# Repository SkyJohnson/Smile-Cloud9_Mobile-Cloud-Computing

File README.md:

# Smile-Cloud9_Mobile-Cloud-Computing
Design for cloud-based rovers to perform image processing over a wireless distributed-computing framework using Jetson Nano and Arduino

This branch contains pictures and screenshots for verification and presentation purposes.

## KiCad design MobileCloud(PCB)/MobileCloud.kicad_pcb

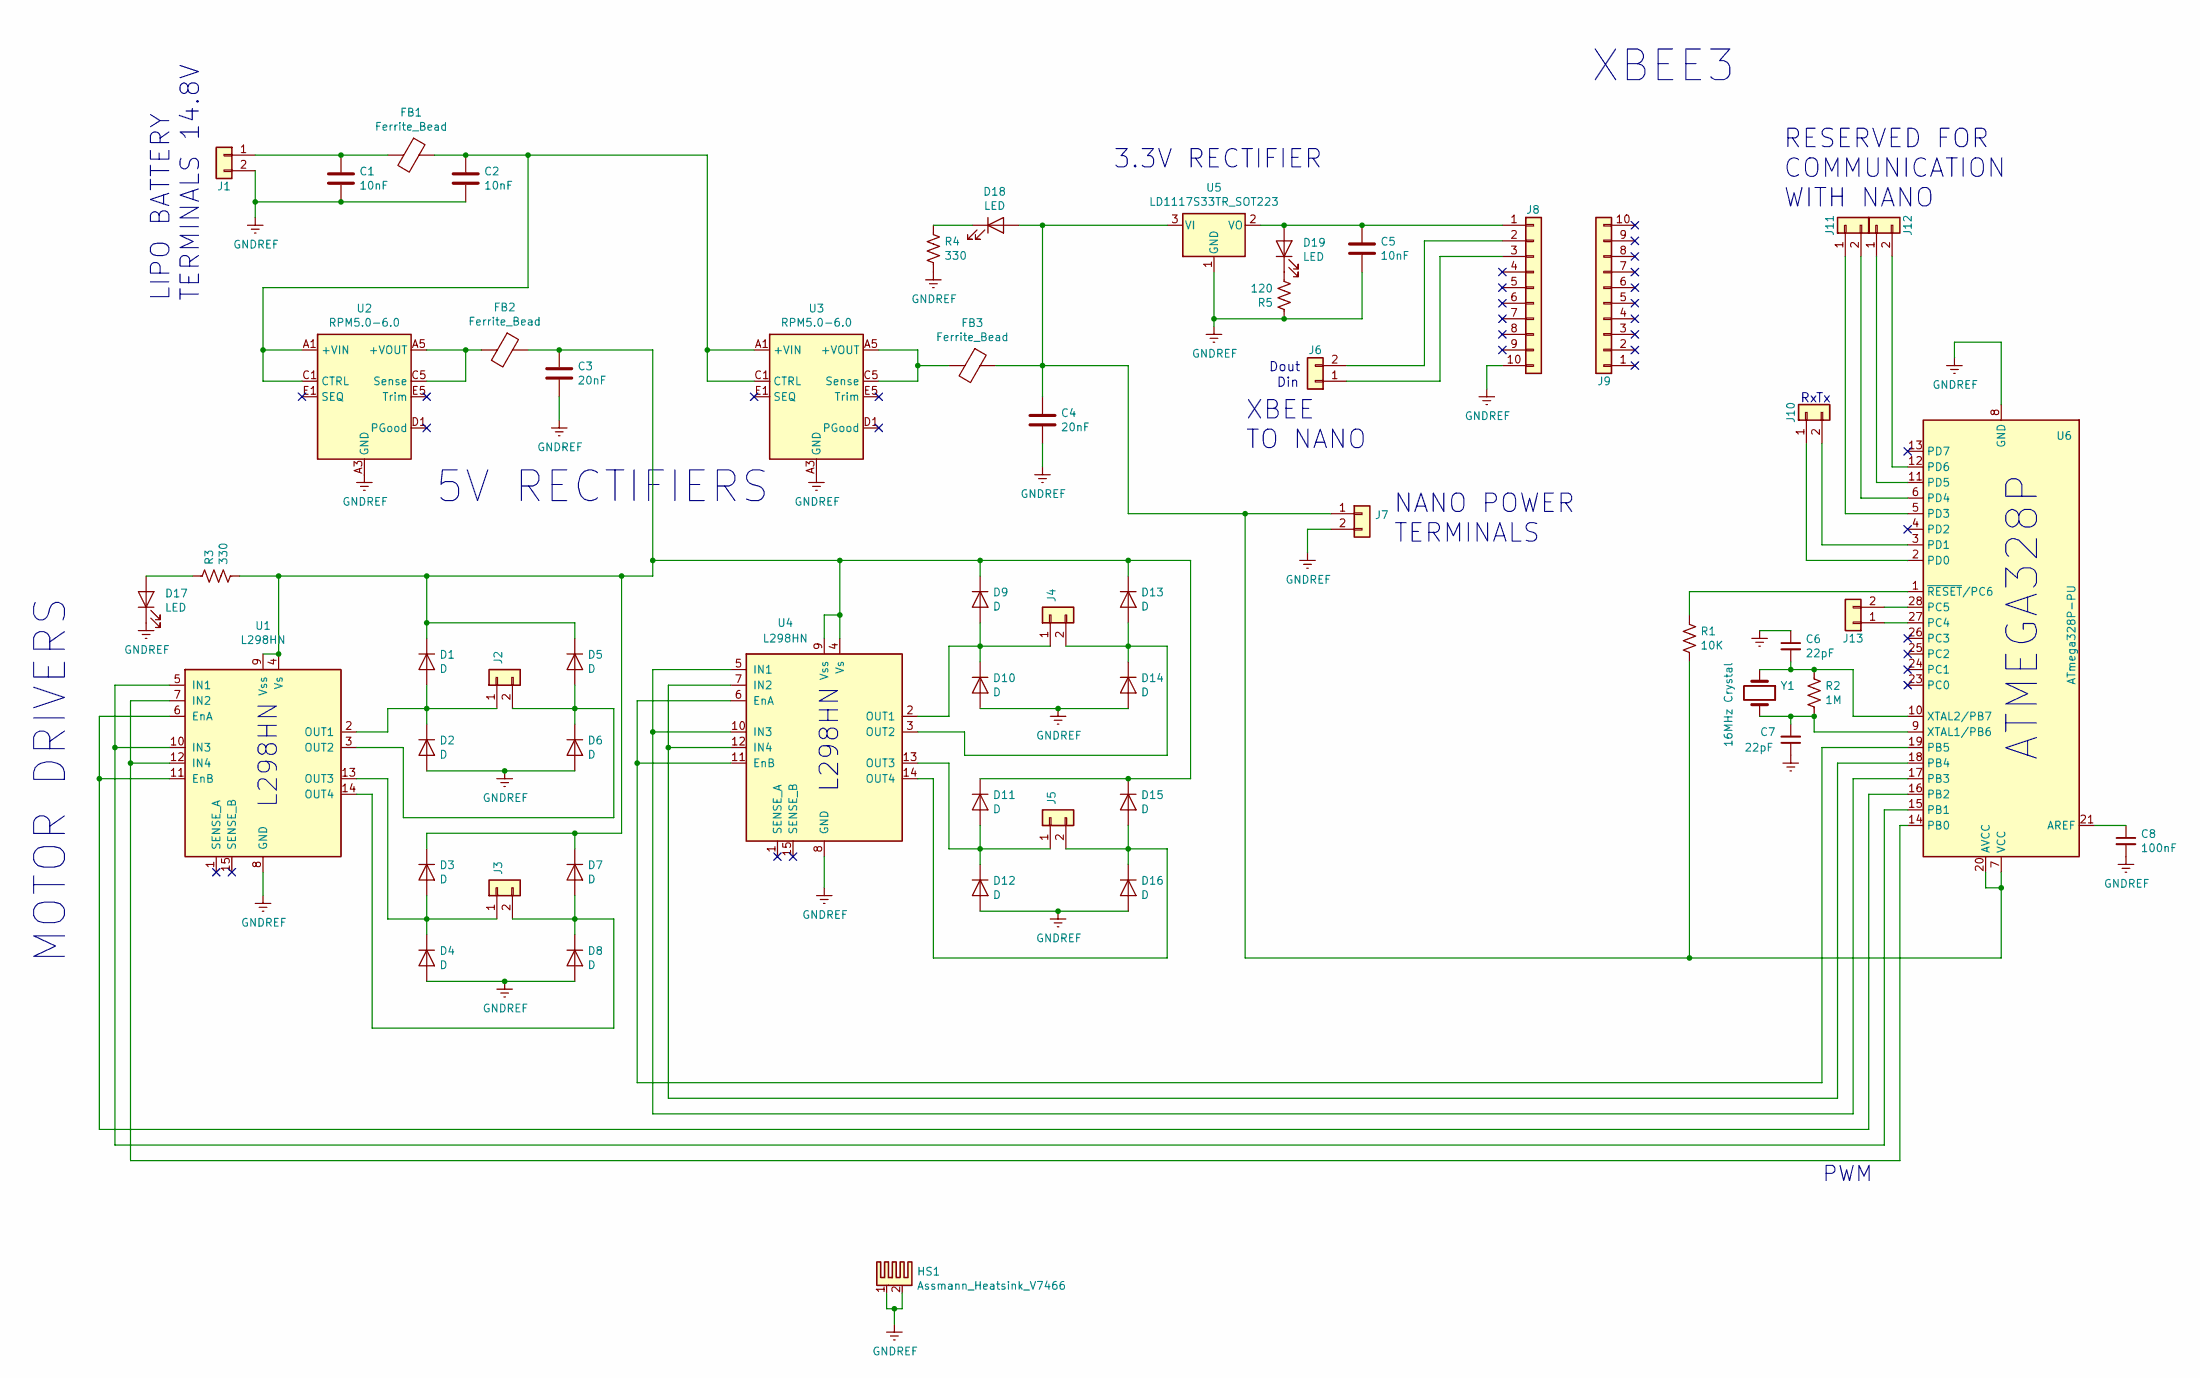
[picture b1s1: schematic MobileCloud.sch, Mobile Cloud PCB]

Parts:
C1, C2, C5: 10nF; C_Disc_D5.0mm_W2.5mm_P5.00mm
C3, C4: 20nF; C_Disc_D5.0mm_W2.5mm_P5.00mm
C6, C7: 22pF; C_Disc_D5.0mm_W2.5mm_P5.00mm
C8: 100nF; C_Disc_D5.0mm_W2.5mm_P5.00mm
D1, D2, D3, D4, D5, D6, D7, D8, D9, D10, D11, D12, D13, D14, D15, D16: D; D_DO-41_SOD81_P10.16mm_Horizontal
D17, D18, D19: LED; LED_D3.0mm
FB1, FB2, FB3: Ferrite_Bead; RESC1812X51N
HS1: Assmann_Heatsink_V7466; V7466x_AssManHeatsink
J1, J7: SolderWirePad_1x02_P5.08mm_Drill1.5mm
J2, J3, J4, J5, J6, J10, J11, J12, J13: PinSocket_1x02_P2.00mm_Vertical
J8, J9: PinSocket_1x10_P2.00mm_Vertical
R1: 10K; R_Axial_DIN0207_L6.3mm_D2.5mm_P10.16mm_Horizontal
R2: 1M; R_Axial_DIN0207_L6.3mm_D2.5mm_P10.16mm_Horizontal
R3, R4: 330; R_Axial_DIN0207_L6.3mm_D2.5mm_P10.16mm_Horizontal
R5: 120; R_Axial_DIN0207_L6.3mm_D2.5mm_P10.16mm_Horizontal
U1, U4: L298HN; TO-220-15_P2.54x2.54mm_StaggerOdd_Lead4.58mm_Vertical
U2, U3: RPM5.0-6.0; Converter_DCDC_RECOM_RPMx.x-x.0
U5: LD1117S33TR_SOT223; SOT-223-3_TabPin2
U6: ATmega328P-PU; DIP-28_W7.62mm
Y1: 16MHz Crystal; Crystal_HC49-U_Vertical

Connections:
GNDREF: C1.2, C2.2, C3.2, C4.2, C5.2, C6.1, C7.1, C8.2, D2.2 (A), D4.2 (A), D6.2 (A), D8.2 (A), D10.2 (A), D12.2 (A), D14.2 (A), D16.2 (A), D17.1 (K), HS1.1, HS1.2, J1.2, J7.2, J8.10, R4.1, R5.2, U1.8 (GND), U2.A3 (GND), U2.A4 (GND), U2.B1 (GND), U2.B2 (GND), U2.B3 (GND), U2.B4 (GND), U2.C2 (GND), U2.C3 (GND), U2.C4 (GND), U2.D2 (GND), U2.D3 (GND), U2.D4 (GND), U2.D5 (GND), U2.E3 (GND), U2.E4 (GND), U3.A3 (GND), U3.A4 (GND), U3.B1 (GND), U3.B2 (GND), U3.B3 (GND), U3.B4 (GND), U3.C2 (GND), U3.C3 (GND), U3.C4 (GND), U3.D2 (GND), U3.D3 (GND), U3.D4 (GND), U3.D5 (GND), U3.E3 (GND), U3.E4 (GND), U4.8 (GND), U5.1 (GND), U6.8 (GND), U6.22 (GND)
unnamed: C1.1, FB1.2, J1.1
unnamed: C2.1, FB1.1, U2.A1 (+VIN), U2.A2 (+VIN), U2.C1 (CTRL), U3.A1 (+VIN), U3.A2 (+VIN), U3.C1 (CTRL)
unnamed: C3.1, D1.1 (K), D3.1 (K), D5.1 (K), D7.1 (K), D9.1 (K), D11.1 (K), D13.1 (K), D15.1 (K), FB2.1, R3.1, U1.4 (Vs), U1.9 (Vss), U4.4 (Vs), U4.9 (Vss)
unnamed: C4.1, D18.2 (A), FB3.1, J7.1, R1.2, U5.3 (VI), U6.7 (VCC), U6.20 (AVCC)
unnamed: C5.1, D19.2 (A), J8.1, U5.2 (VO)
unnamed: C6.2, R2.2, U6.10 (XTAL2/PB7), Y1.1
unnamed: C7.2, R2.1, U6.9 (XTAL1/PB6), Y1.2
unnamed: C8.1, U6.21 (AREF)
unnamed: D1.2 (A), D2.1 (K), J2.1, U1.2 (OUT1)
unnamed: D3.2 (A), D4.1 (K), J3.1, U1.13 (OUT3)
unnamed: D5.2 (A), D6.1 (K), J2.2, U1.3 (OUT2)
unnamed: D7.2 (A), D8.1 (K), J3.2, U1.14 (OUT4)
unnamed: D9.2 (A), D10.1 (K), J4.1, U4.2 (OUT1)
unnamed: D11.2 (A), D12.1 (K), J5.1, U4.13 (OUT3)
unnamed: D13.2 (A), D14.1 (K), J4.2, U4.3 (OUT2)
unnamed: D15.2 (A), D16.1 (K), J5.2, U4.14 (OUT4)
unnamed: D17.2 (A), R3.2
unnamed: D18.1 (K), R4.2
unnamed: D19.1 (K), R5.1
unnamed: FB2.2, U2.A5 (+VOUT), U2.B5 (+VOUT), U2.C5 (Sense)
unnamed: FB3.2, U3.A5 (+VOUT), U3.B5 (+VOUT), U3.C5 (Sense)
unnamed: J6.1, J8.3
unnamed: J6.2, J8.2
unnamed: J10.1, U6.2 (PD0)
unnamed: J10.2, U6.3 (PD1)
unnamed: J11.1, U6.5 (PD3)
unnamed: J11.2, U6.6 (PD4)
unnamed: J12.1, U6.11 (PD5)
unnamed: J12.2, U6.12 (PD6)
unnamed: J13.1, U6.27 (PC4)
unnamed: J13.2, U6.28 (PC5)
unnamed: R1.1, U6.1 (~RESET~/PC6)
unnamed: U1.5 (IN1), U1.10 (IN3), U6.15 (PB1)
unnamed: U1.6 (EnA), U1.11 (EnB), U6.16 (PB2)
unnamed: U1.7 (IN2), U1.12 (IN4), U6.14 (PB0)
unnamed: U4.5 (IN1), U4.10 (IN3), U6.17 (PB3)
unnamed: U4.6 (EnA), U4.11 (EnB), U6.19 (PB5)
unnamed: U4.7 (IN2), U4.12 (IN4), U6.18 (PB4)

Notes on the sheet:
XBEE3
XBEE TO NANO
LIPO BATTERY TERMINALS 14.8V
L298HN
3.3V RECTIFIER
MOTOR DRIVERS
5V RECTIFIERS
ATMEGA328P
NANO POWER TERMINALS
Dout
Din
PWM
RESERVED FOR COMMUNICATION WITH NANO

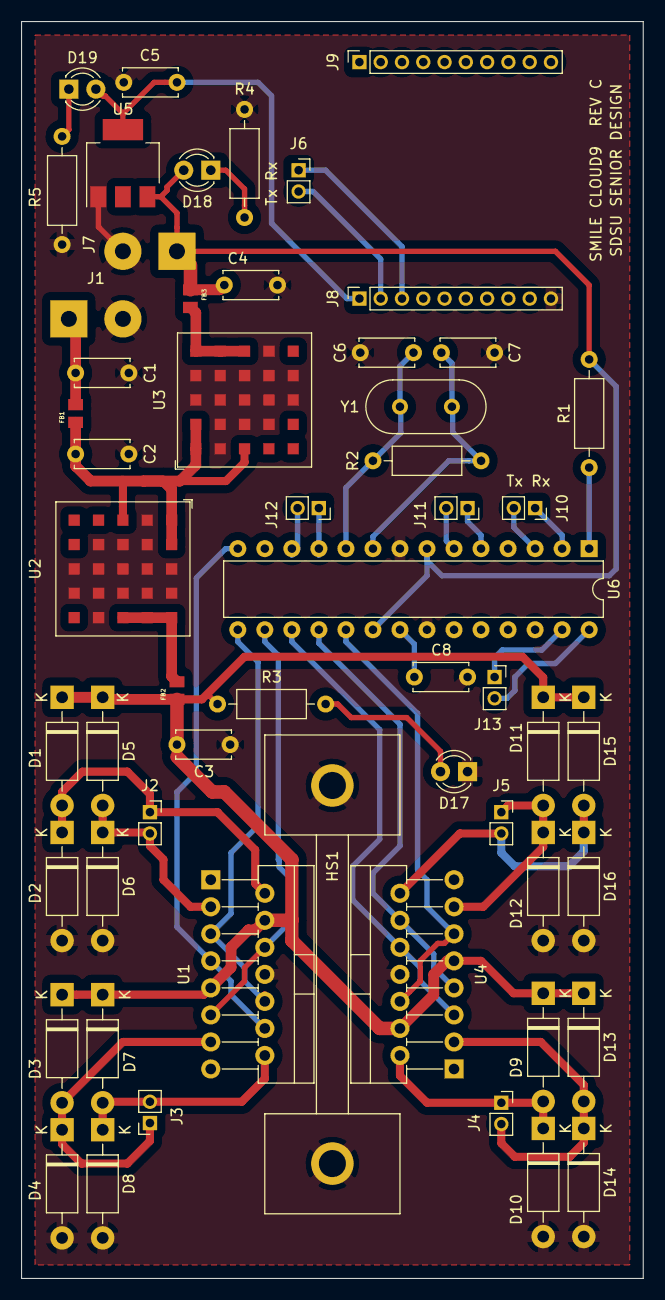
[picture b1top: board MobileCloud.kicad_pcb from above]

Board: 2 copper layers, 58.4 x 118.1 mm, 56 parts (0 on the bottom side), 39 nets.

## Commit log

2020-02-06 Add files via upload
    Python code from "Training a classifier tutorial."
2020-02-18 Add files via upload
    Assmann Heatsink
    V7466x - generic size
    PCB Footprint for KiCad
2020-02-18 Deleted uneeded files
2020-03-09 Create UART Python
2020-03-20 Create hostsFileContent_master
2020-04-17 Rename distProgramOverMPI_2.py to DistProgramOverMPI_2.py
2020-04-17 Rename distProgramOverMPI_3.py to DistProgramOverMPI_3.py
2020-04-23 More features added compared to v6
    Now able to measure node execution time, obtain and average the node weights, and load those average weights to the master node.
2020-04-23 trainNetwork with horovod wrapper - untested
2020-04-23 Fixed some things to execute, but still gives error
    Added hvd.init in the beginning
2020-04-24 Non-distributed version of object detection network
2020-04-24 Distributed version of object detection network (working)
2020-04-24 Had the wrong code in this file, fixed it
2020-04-29 Create Receiver2.py
    Write the messages received into a file, to speed up transmission. When data was not in a file, the received messages will sometimes come in too fast before the data is processed into a matrix.
    1.Read message
    2. Save message into a file
    3. Keep receiving and saving messages into file until the transmission is complete
    4. Append all data from the file into a matrix
2020-05-01 changed dataset. Accuracy is very low for some reason
    Re-did the model using a dataset of household objects.
    Link to download dataset: http://hemanthdv.org/OfficeHome-Dataset/
    Only used backpack, bed, bottle, calculator, chair, computer, keyboard, mouse, notebook, pen, pencil, and telephone categories under OfficeHomeDataset_10072016 > Real World and copied into a new fold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
2020-05-01 Same as v4 but modified to work for nano
2020-05-01 Same as v4, but modified to work for nano
